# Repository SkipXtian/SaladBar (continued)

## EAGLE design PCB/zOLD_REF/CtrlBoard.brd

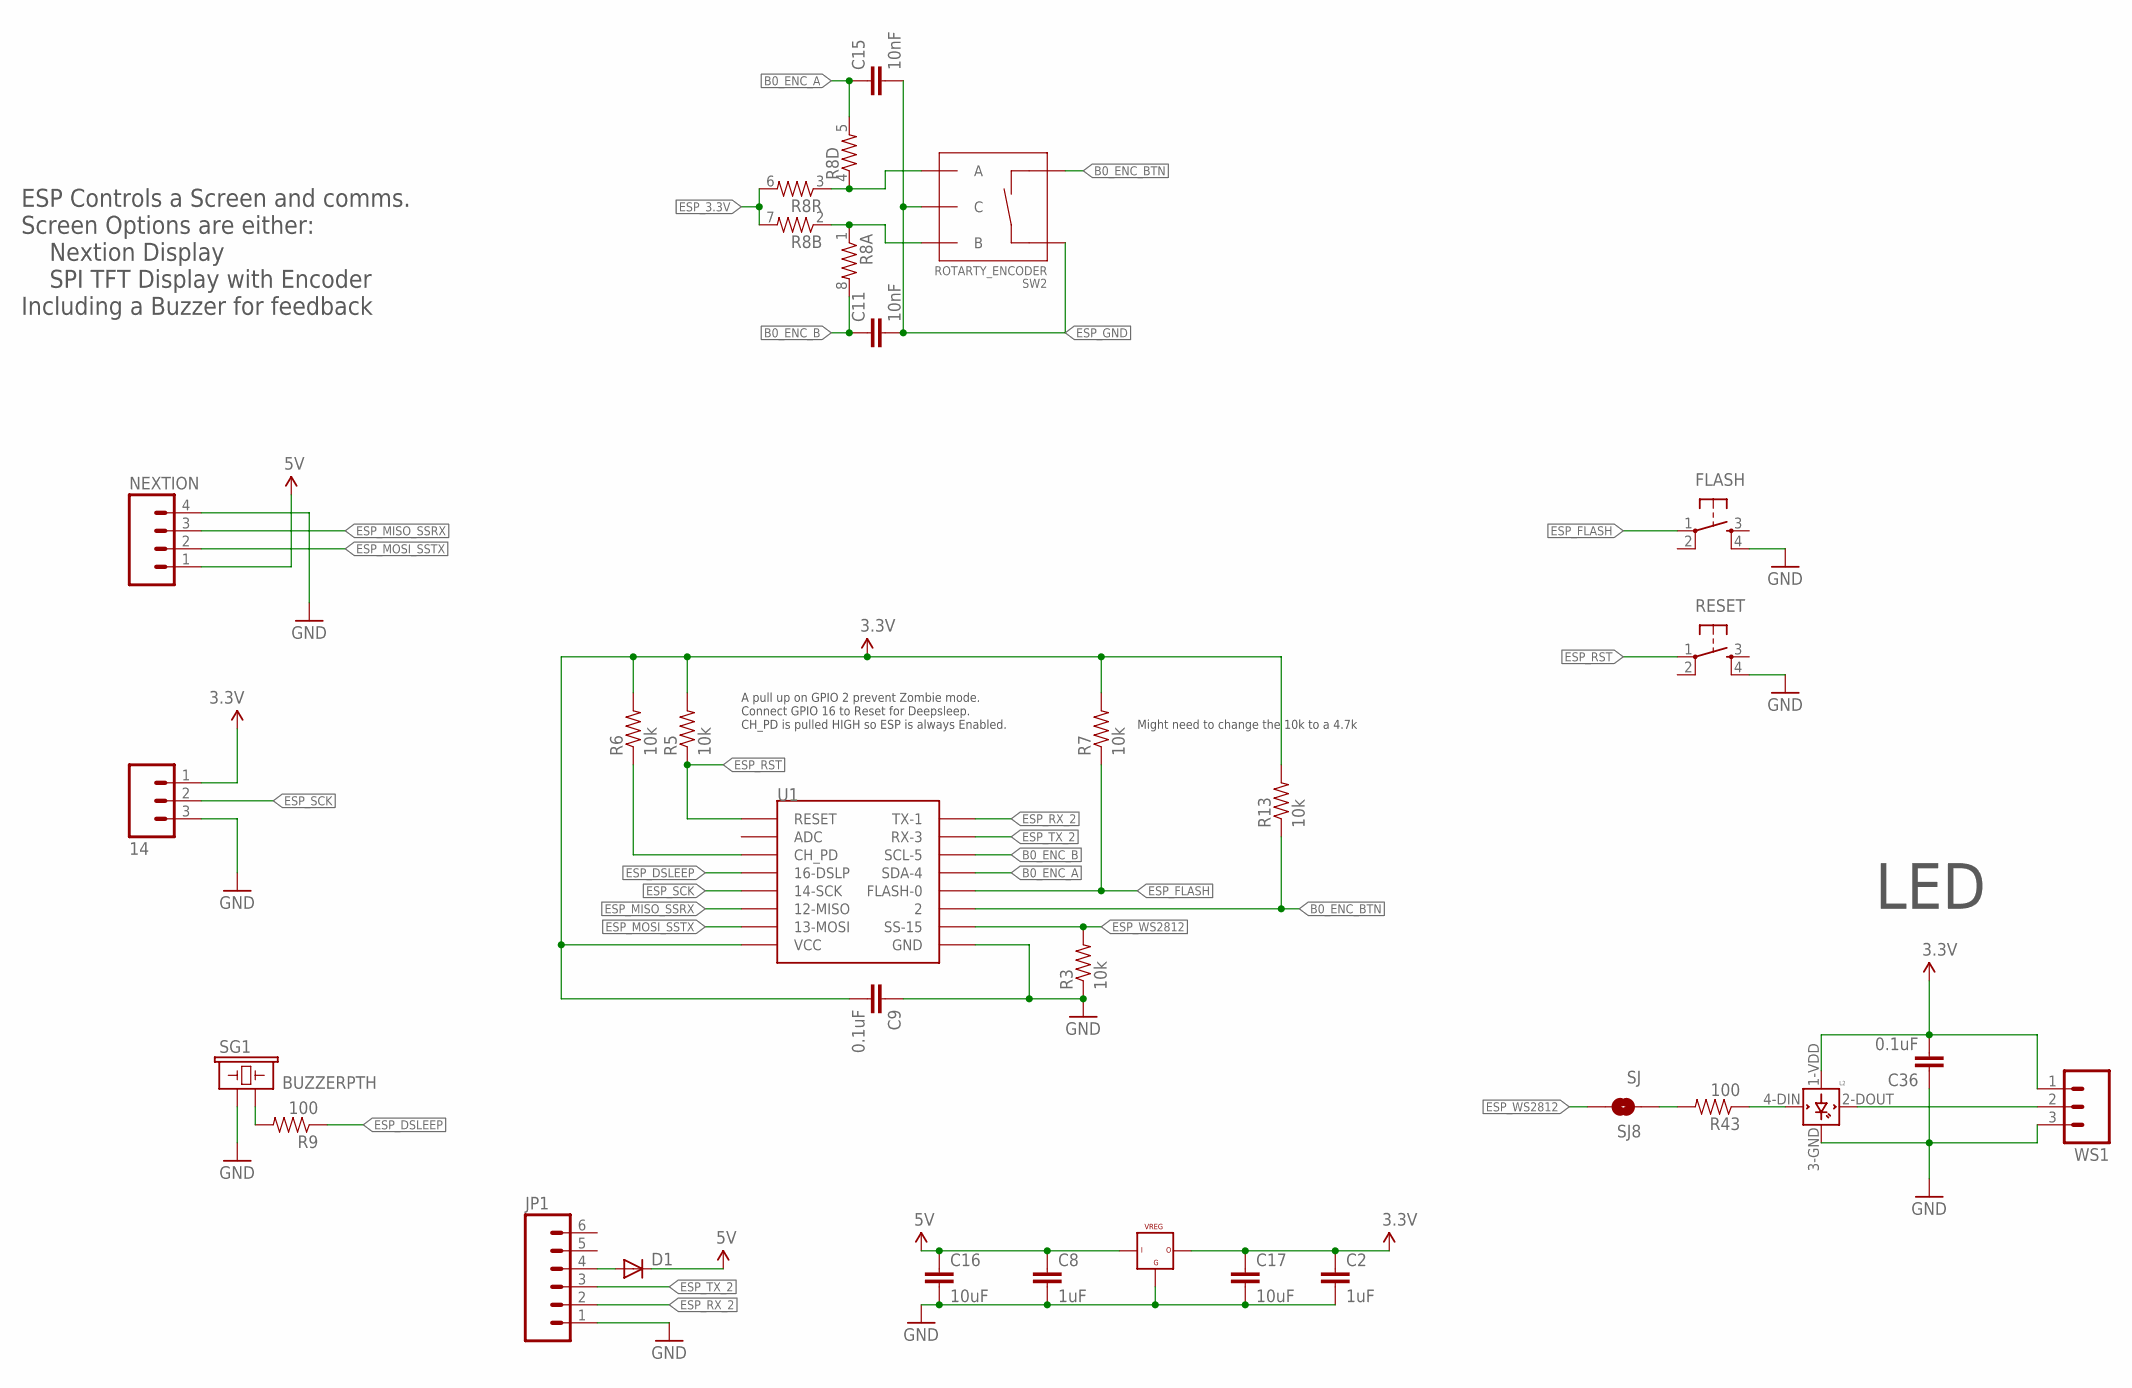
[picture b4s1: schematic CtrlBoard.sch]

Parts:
14: M03PTH; 1X03
C2, C8: 1uF; 0805
C9, C36: 0.1uF; 0805
C11, C15: 10nF; 0805
C16, C17: 10uF; 0805
D1: DIODESOD; SOD-323
FLASH: TAC_SWITCHSMD; TACTILE_SWITCH_SMD
JP1: M06SILK_FEMALE_PTH; 1X06
L2: WS2812B
NEXTION: M041X04_NO_SILK; 1X04_NO_SILK
R3, R5, R6, R7, R13: 10k; 0805
R8: RESISTOR-ARRAY0603-ARV; 0603-ARV
R9, R43: 100; 0805
RESET: TAC_SWITCHSMD; TACTILE_SWITCH_SMD
SG1: BUZZERPTH; BUZZER-12MM
SJ8: SJ; SJ_2S-NO
SW2: ROTARTY_ENCODER; ROTARY_ENC_PLAIN
U1: ESP12SMD; ESP12-SMD
U$3: VREG_3V3; DPACK
WS1: M03PTH; 1X03

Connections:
B0_ENC_A: C15.1, R8.5 (2), U1.GPIO4 (SDA-4)
B0_ENC_B: C11.1, R8.8 (2), U1.GPIO5 (SCL-5)
B0_ENC_BTN: R13.1, SW2.SW-, U1.GPIO2 (2)
ESP_3.3V: 14.1, C2.1, C9.2, C17.1, C36.2, L2.1-VDD (VDD), R5.2, R6.2, R7.2, R8.6 (2), R8.7 (2), R13.2, U1.VCC, U$3.2 (3), WS1.1
ESP_5V: C8.1, C16.1, D1.1 (C), NEXTION.1, U$3.3 (1)
ESP_DSLEEP: R9.1, U1.GPIO16 (16-DSLP)
ESP_FLASH: FLASH.1, R7.1, U1.GPIO0 (FLASH-0)
ESP_GND: 14.3, C2.2, C8.2, C9.1, C11.2, C15.2, C16.2, C17.2, C36.1, FLASH.4, JP1.1, L2.3-GND (GND), NEXTION.4, R3.1, RESET.4, SG1.+ (1), SW2.C, SW2.SW+, U1.GND, U$3.1 (2), WS1.3
ESP_MISO_SSRX: NEXTION.3, U1.GPIO12 (12-MISO)
ESP_MOSI_SSTX: NEXTION.2, U1.GPIO13 (13-MOSI)
ESP_RST: R5.1, RESET.1, U1.RESET
ESP_RX_2: JP1.2, U1.TXD0 (TX-1)
ESP_SCK: 14.2, U1.GPIO14 (14-SCK)
ESP_TX_2: JP1.3, U1.RXD0 (RX-3)
ESP_WS2812: R3.2, SJ8.2, U1.GPIO15 (SS-15)
unnamed: R6.1, U1.CH_PD
unnamed: D1.2 (A), JP1.4
unnamed: R8.1, R8.2 (1), SW2.B
unnamed: R9.2, SG1.- (2)
unnamed: R8.3 (1), R8.4 (1), SW2.A
unnamed: L2.4-DIN (DIN), R43.1
unnamed: L2.2-DOUT (DOUT), WS1.2
unnamed: R43.2, SJ8.1

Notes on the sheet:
A pull up on GPIO 2 prevent Zombie mode. Connect GPIO 16 to Reset for Deepsleep. CH_PD is pulled HIGH so ESP is always Enabled.
Might need to change the 10k to a 4.7k
ESP Controls a Screen and comms. Screen Options are either: Nextion Display SPI TFT Display with Encoder Including a Buzzer for feedback
LED

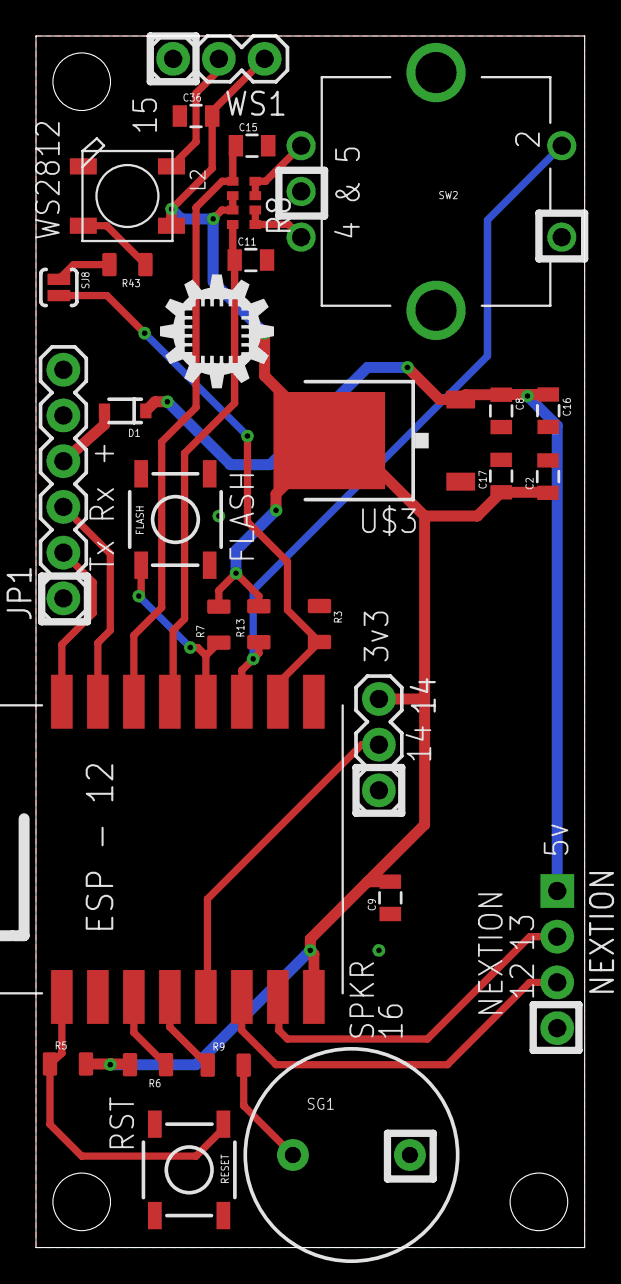
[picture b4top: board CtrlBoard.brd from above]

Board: 2 copper layers, 30.5 x 67.3 mm, 31 parts (1 on the bottom side), 23 nets.

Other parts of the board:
U$19: GCTS_X0.75
U$25: ID_LOGO_X0.25

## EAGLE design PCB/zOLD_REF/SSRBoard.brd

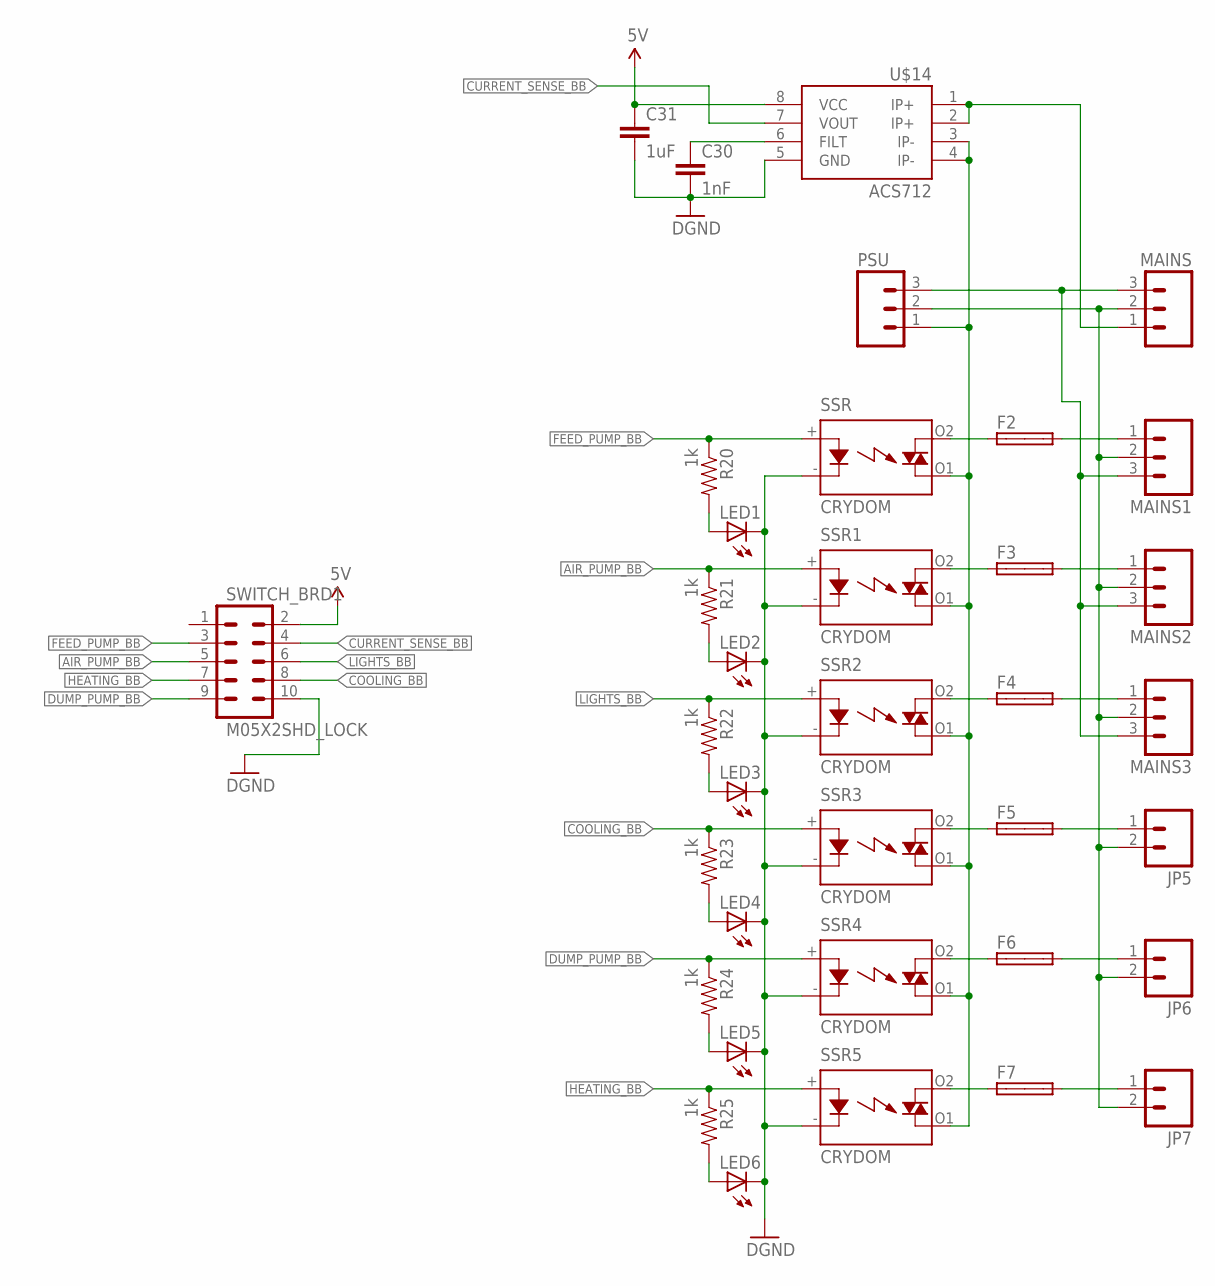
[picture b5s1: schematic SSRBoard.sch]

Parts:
C30: 1nF; 0805
C31: 1uF; 0805
F2, F3, F4, F5, F6, F7: SHK20L
JP5, JP6, JP7: M025MM; SCREWTERMINAL-5MM-2
LED1, LED2, LED3, LED4, LED5, LED6: LEDSML0805; SML0805
MAINS, MAINS1, MAINS2, MAINS3: M03-SCREW-5MM; SCREWTERMINAL-5MM-3
PSU: M03-SCREW-5MM; SCREWTERMINAL-5MM-3
R20, R21, R22, R23, R24, R25: 1k; 0805
SSR: CRYDOM; AQG
SSR1, SSR2, SSR3, SSR4, SSR5: CRYDOM; AQG; MPN AQG22224
SWITCH_BRD1: M05X2SHD_LOCK; 2X5-SHROUDED_LOCK
U$14: ACS712; SO08

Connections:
5V_BB: C31.1, SWITCH_BRD1.2, U$14.8 (VCC)
AIR_PUMP_BB: R21.1, SSR1.+ (A), SWITCH_BRD1.5
COOLING_BB: R23.1, SSR3.+ (A), SWITCH_BRD1.8
CURRENT_SENSE_BB: SWITCH_BRD1.4, U$14.7 (VOUT)
DUMP_PUMP_BB: R24.1, SSR4.+ (A), SWITCH_BRD1.9
FEED_PUMP_BB: R20.1, SSR.+ (A), SWITCH_BRD1.3
GND_BB: C30.2, C31.2, LED1.C, LED2.C, LED3.C, LED4.C, LED5.C, LED6.C, SSR.- (K), SSR1.- (K), SSR2.- (K), SSR3.- (K), SSR4.- (K), SSR5.- (K), SWITCH_BRD1.10, U$14.5 (GND)
HEATING_BB: R25.1, SSR5.+ (A), SWITCH_BRD1.7
LIGHTS_BB: R22.1, SSR2.+ (A), SWITCH_BRD1.6
MAIN_ACTIVE: PSU.1, SSR.O1 (DS2), SSR1.O1 (DS2), SSR2.O1 (DS2), SSR3.O1 (DS2), SSR4.O1 (DS2), SSR5.O1 (DS2), U$14.3 (IP-), U$14.4 (IP-)
MAIN_ACTIVE1: MAINS.1, U$14.1 (IP+), U$14.2 (IP+)
MAIN_EARTH: MAINS.3, MAINS1.3, MAINS2.3, MAINS3.3, PSU.3
MAIN_NETURAL: JP5.2, JP6.2, JP7.2, MAINS.2, MAINS1.2, MAINS2.2, MAINS3.2, PSU.2
unnamed: F3.1A, SSR1.O2 (DS1)
unnamed: F2.1A, SSR.O2 (DS1)
unnamed: F4.1A, SSR2.O2 (DS1)
unnamed: F5.1A, SSR3.O2 (DS1)
unnamed: F6.1A, SSR4.O2 (DS1)
unnamed: F7.1A, SSR5.O2 (DS1)
unnamed: LED1.A, R20.2
unnamed: F2.2A, MAINS1.1
unnamed: F3.2A, MAINS2.1
unnamed: F4.2A, MAINS3.1
unnamed: F5.2A, JP5.1
unnamed: F6.2A, JP6.1
unnamed: F7.2A, JP7.1
unnamed: LED2.A, R21.2
unnamed: LED3.A, R22.2
unnamed: LED4.A, R23.2
unnamed: C30.1, U$14.6 (FILT)
unnamed: LED5.A, R24.2
unnamed: LED6.A, R25.2

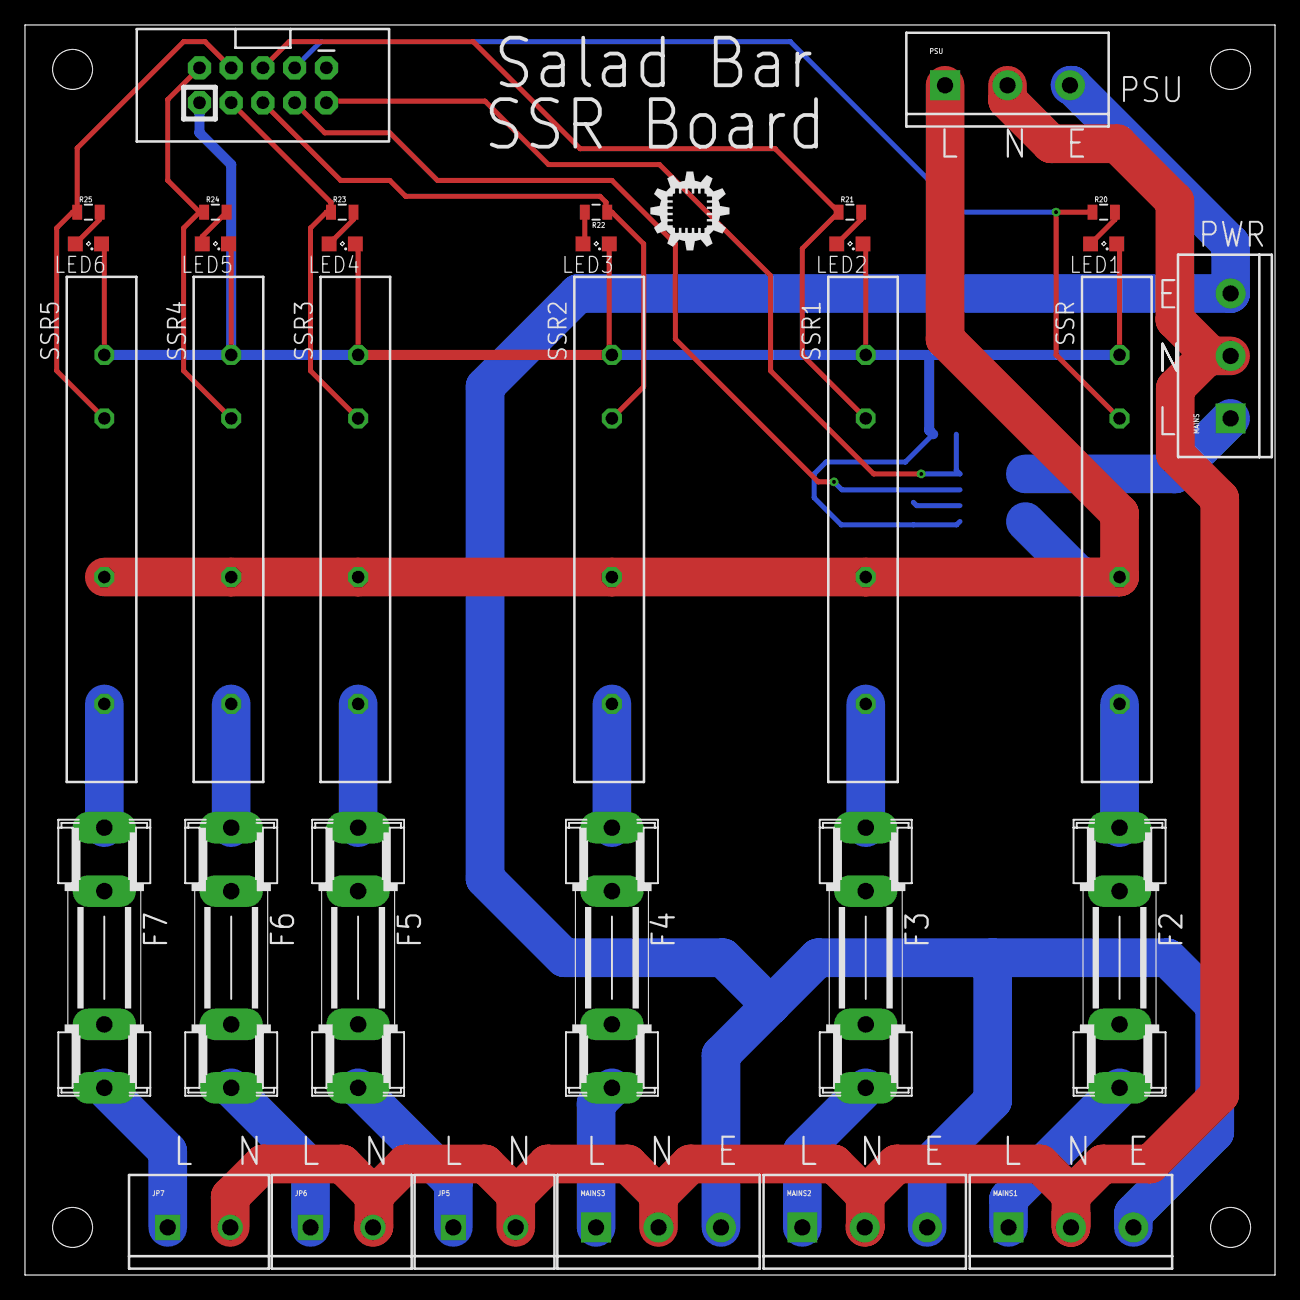
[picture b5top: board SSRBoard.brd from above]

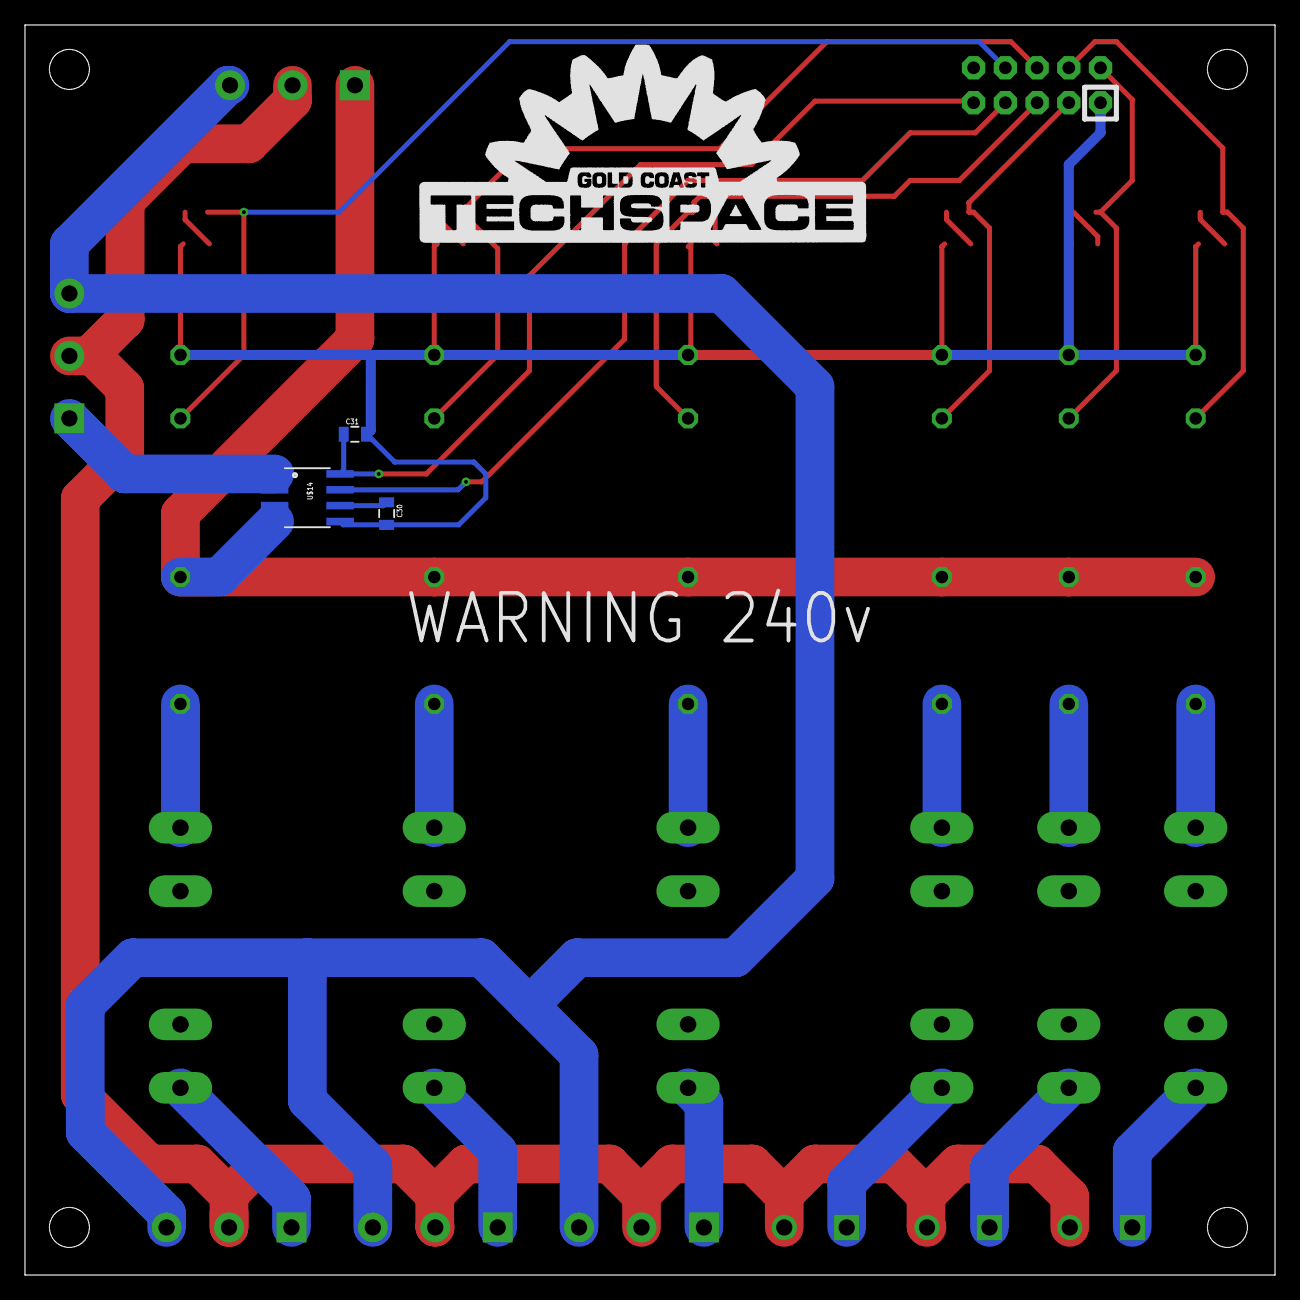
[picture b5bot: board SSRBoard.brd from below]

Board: 2 copper layers, 100.1 x 100.1 mm, 38 parts (4 on the bottom side), 32 nets.

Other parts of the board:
U$21: GCTS_X0.75
U$24: ID_LOGO_X0.25

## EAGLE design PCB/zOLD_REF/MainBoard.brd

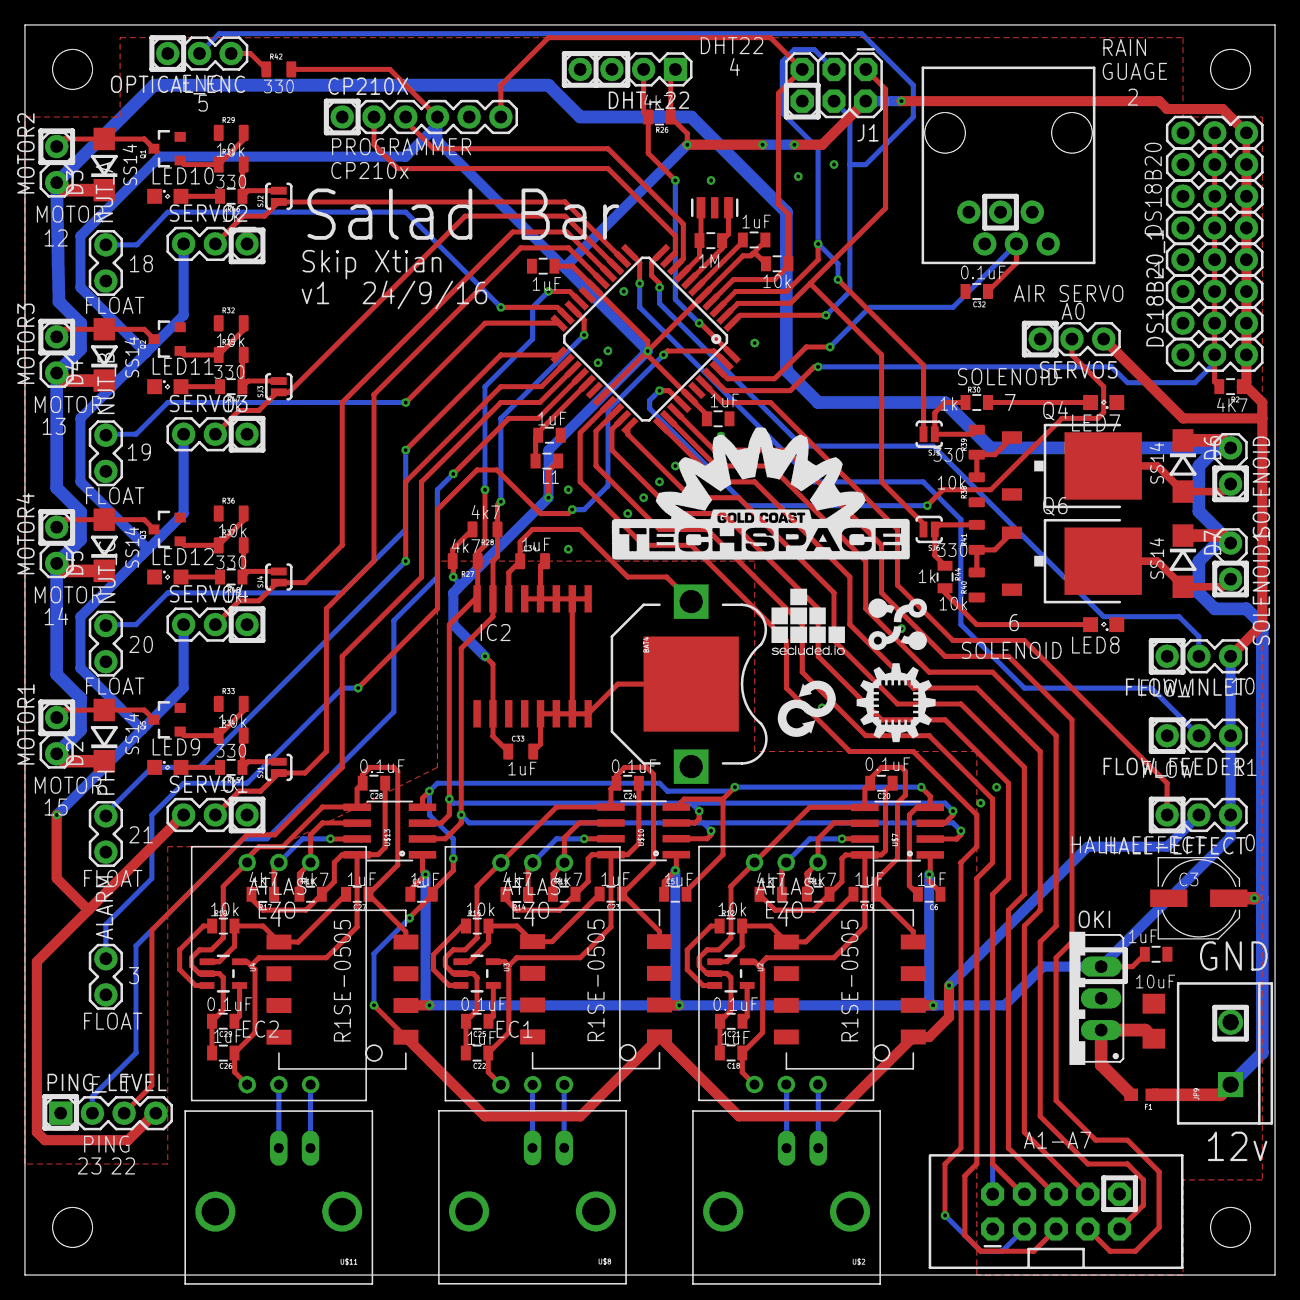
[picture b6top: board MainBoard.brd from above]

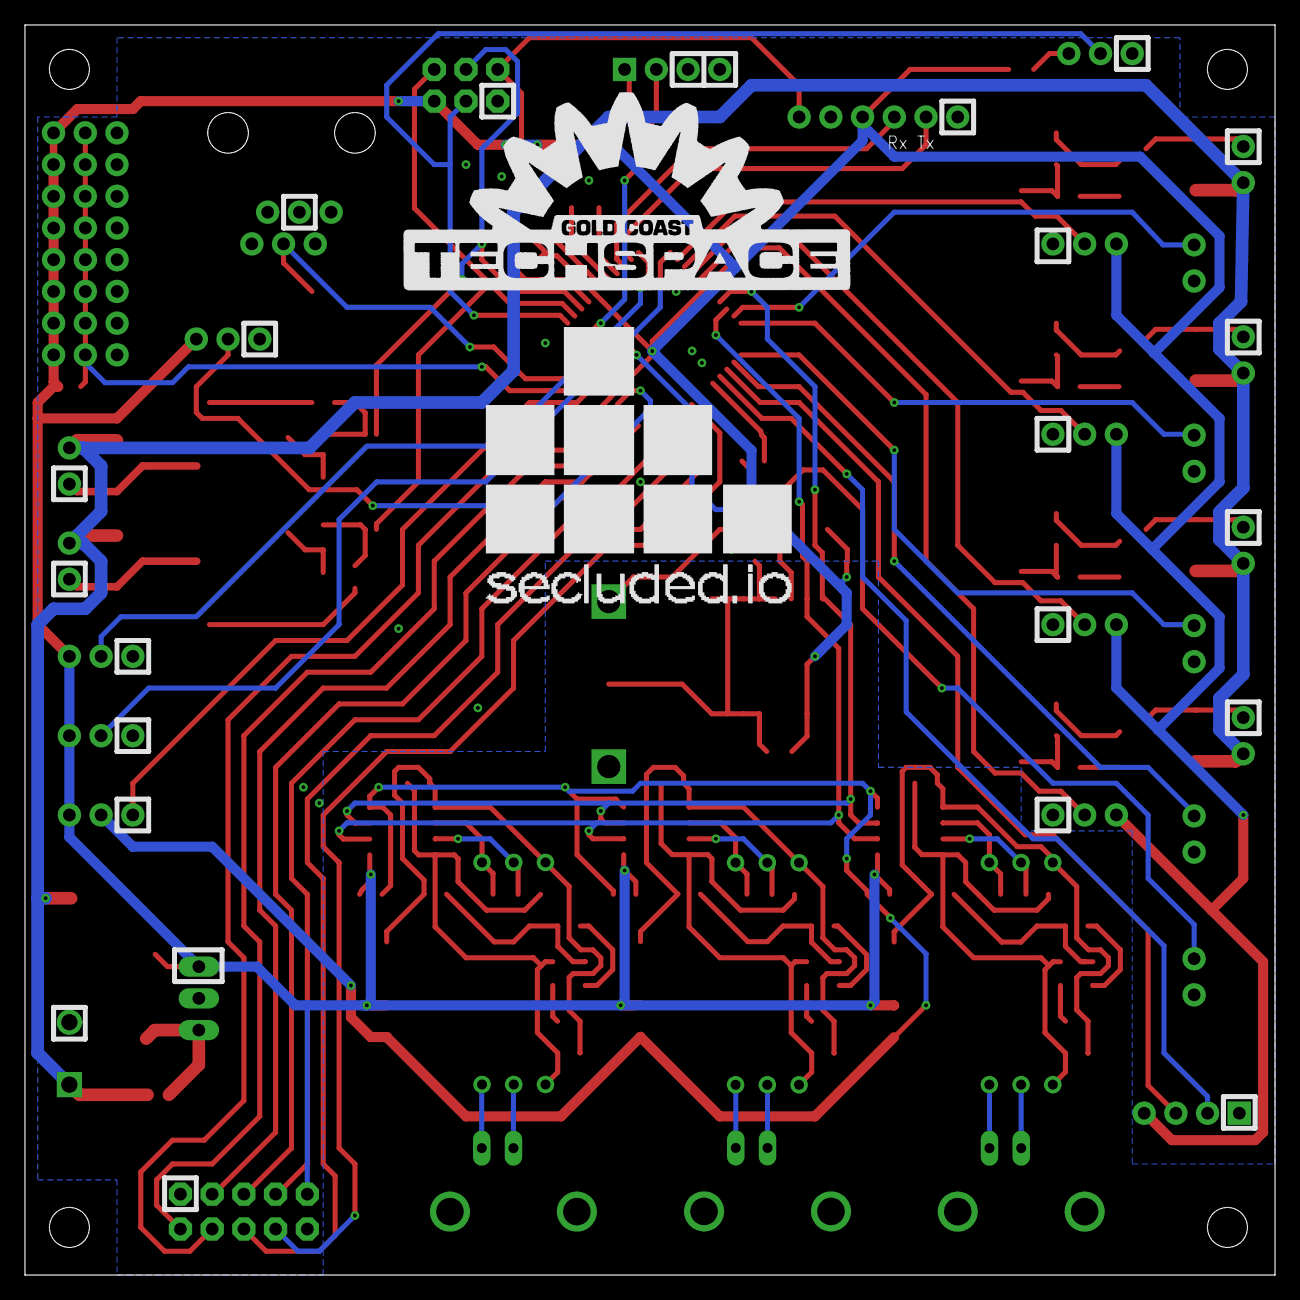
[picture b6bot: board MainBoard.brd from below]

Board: 2 copper layers, 100.1 x 100.1 mm, 147 parts (2 on the bottom side), 93 nets.

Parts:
ALARM: 1X02_LOCK
BAT4: BATTCON_12MM_PTH
C1: 10uF; 1206
C3: PANASONIC_D
C4, C5, C6, C7, C10, C12, C13, C14, C18, C19, C22, C23, C26, C27, C33, C34: 1uF; 0805
C20, C21, C24, C25, C28, C29, C32: 0.1uF; 0805
CP210X: 1X06
D2, D3, D4, D5, D6, D7: SS14; DO214BA
DHT-22: 1X04
DS18B20_1, DS18B20_2, DS18B20_3, DS18B20_4, DS18B20_5, DS18B20_6, DS18B20_7, DS18B20_8: 1X03
EC, EC1: ATLAS-EZO
EC2: ATLAS-EZO
F1: PTC0603; 0603
FLOW_FEEDER: 1X03
FLOW_INLET: 1X03
HALL-EFFECT: 1X03
IC1: ATMEGA644A; TQFP44
IC2: DS3231/SO; SO16W
J1: AVR_SPI_PRG_6PTH; 2X3
JP9: SCREWTERMINAL-5MM-2
L1: 0805
LED7, LED8, LED9, LED10, LED11, LED12: SML0805
MOTOR1, MOTOR2, MOTOR3, MOTOR4: 1X02_LOCK
NUT_A: 1X02_LOCK
NUT_B: 1X02_LOCK
NUT_C: 1X02_LOCK
OKI: 78XXS
OPTICAL_ENC: 1X03
PH: 1X02_LOCK
PING_LEVEL: 1X04
Q1, Q2, Q3, Q5: NTD5867NLT4G; SOT23-3
Q4, Q6: NTD5867NLT4G; DPACK
R1, R12, R16, R19, R29, R32, R33, R36, R38, R40: 10k; 0805
R2: 4K7; 0805
R4: 1M; 0805
R10, R11, R14, R15, R17, R18, R26, R27, R28: 4k7; 0805
R30, R44, R45, R46, R47, R48: 1k; 0805
R31, R34, R35, R37, R39, R41, R42: 330; 0805
RAIN: RJ11-6PTH; RJ11-6
SERVO1, SERVO2, SERVO3, SERVO4, SERVO5: 1X03
SJ1, SJ2, SJ3, SJ4, SJ5, SJ6: SJ; SJ_2S-NO
SOLENOID, SOLENOID1: 1X02_LOCK
SWITCH_BRD2: M05X2SHD_LOCK; 2X5-SHROUDED_LOCK
U2, U3, U4: TPS73150DBVT; SOT23-5
U$1: REFACTORLOOP
U$2, U$8, U$11: BNCPTH; BNC
U$6, U$9, U$12: R1SE-0505
U$7, U$10, U$13: SI860X; SO08
U$15: SECLUDED_5MM
U$17: ESPDUINO_LOGO_5MM
U$18: GCTS_X0.5_TSILK
U$20: ID_LOGO_X0.25
U$22: GCTS_X0.75
U$23: SECLUDED_25MM
Y1: FREQCTRL_RESONATORSMD; FREQCTRL_RESONATOR-SMD

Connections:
5V: C4.1, C5.1, C6.1, C7.1, C12.1, C13.1, C14.1, C33.1, CP210X.4, DHT-22.1, DS18B20_1.1, DS18B20_2.1, DS18B20_3.1, DS18B20_4.1, DS18B20_5.1, DS18B20_6.1, DS18B20_7.1, DS18B20_8.1, FLOW_FEEDER.1, FLOW_INLET.1, HALL-EFFECT.1, IC1.5, IC1.17, IC1.29, IC1.38, IC2.2, J1.2, L1.1, OKI.OUT, PING_LEVEL.4, R1.1, R2.1, R26.1, R27.2, R28.2, R42.2, SERVO1.1, SERVO2.1, SERVO3.1, SERVO4.1, SERVO5.1, SWITCH_BRD2.2, U$6.VCC, U$7.1, U$9.VCC, U$10.1, U$12.VCC, U$13.1
12.0V: C3.+, D2.C, D3.C, D4.C, D5.C, D6.C, D7.C, F1.1, JP9.1, MOTOR1.1, MOTOR2.1, MOTOR3.1, MOTOR4.1, SOLENOID.1, SOLENOID1.1
AIR: IC1.37, SERVO5.2
AIR_PUMP: IC1.31, SWITCH_BRD2.5
COOLING: IC1.34, SWITCH_BRD2.8
CURRENT_SENSE: IC1.32, SWITCH_BRD2.4
D1: D3.A, MOTOR2.2, Q1.3
D2: D4.A, MOTOR3.2, Q2.3
D3: D5.A, MOTOR4.2, Q3.3
D4: D2.A, MOTOR1.2, Q5.3
D5: D6.A, Q4.2, SOLENOID.2
D6: D7.A, Q6.2, SOLENOID1.2
DHT22: DHT-22.2, IC1.44, R26.2
DUMP_HALL-EFFECT: HALL-EFFECT.3, IC1.40
DUMP_PUMP: IC1.35, SWITCH_BRD2.9
FEEDER_FLOW: FLOW_FEEDER.2, IC1.12
FEED_PUMP: IC1.30, SWITCH_BRD2.3
FLOAT_LEVEL-ALARM: ALARM.1, IC1.43
FLOAT_NUT_A: IC1.21, NUT_A.1
FLOAT_NUT_B: IC1.22, NUT_B.1
FLOAT_NUT_C: IC1.23, NUT_C.1
FLOAT_PH_DOWN: IC1.24, PH.1
GND: ALARM.2, BAT4.GND, C1.2, C3.-, C4.2, C5.2, C6.2, C7.2, C10.2, C12.2, C13.2, C14.2, C32.2, C33.2, C34.2, CP210X.1, DHT-22.3, DHT-22.4, DS18B20_1.3, DS18B20_2.3, DS18B20_3.3, DS18B20_4.3, DS18B20_5.3, DS18B20_6.3, DS18B20_7.3, DS18B20_8.3, FLOW_FEEDER.3, FLOW_INLET.3, HALL-EFFECT.2, IC1.6, IC1.18, IC1.28, IC1.39, IC2.5, IC2.6, IC2.7, IC2.8, IC2.9, IC2.10, IC2.11, IC2.12, IC2.13, J1.6, JP9.2, LED7.C, LED8.C, LED9.C, LED10.C, LED11.C, LED12.C, NUT_A.2, NUT_B.2, NUT_C.2, OKI.GND, OPTICAL_ENC.3, PH.2, PING_LEVEL.1, Q1.2, Q2.2, Q3.2, Q4.3, Q5.2, Q6.3, R29.1, R32.1, R33.1, R36.1, R38.1, R40.1, RAIN.4, SERVO1.3, SERVO2.3, SERVO3.3, SERVO4.3, SERVO5.3, SWITCH_BRD2.1, SWITCH_BRD2.10, U$6.GND, U$7.4, U$9.GND, U$10.4, U$12.GND, U$13.4, Y1.2
HEATING: IC1.36, SWITCH_BRD2.7
INLET_FLOW: FLOW_INLET.2, IC1.11
LEVEL_PING-ECHO: IC1.26, PING_LEVEL.2
LEVEL_PING-TRIG: IC1.25, PING_LEVEL.3
LIGHTS: IC1.33, SWITCH_BRD2.6
unnamed: IC1.7, R4.2, Y1.1
unnamed: IC1.8, R4.1, Y1.3
unnamed: EC.PRA, U$2.GND
unnamed: EC.PRB, U$2.S
unnamed: C18.2, C19.1, C20.2, C21.2, EC.GND, U2.2, U$6.ISO_GND, U$7.5
unnamed: C18.1, C20.1, EC.VCC, R10.2, R11.2, U2.5, U$7.8
unnamed: EC.RX, R11.1, U$7.6
unnamed: C10.1, IC1.27, L1.2
unnamed: EC.TX, R10.1, U$7.7
unnamed: R12.1, U2.3
unnamed: C19.2, R12.2, U2.1, U$6.ISO_VCC
unnamed: C1.1, F1.2, OKI.IN
unnamed: EC1.PRB, U$8.S
unnamed: C21.1, U2.4
unnamed: C22.2, C23.1, C24.2, C25.2, EC1.GND, U3.2, U$9.ISO_GND, U$10.5
unnamed: C22.1, C24.1, EC1.VCC, R14.2, R15.2, U3.5, U$10.8
unnamed: EC1.PRA, U$8.GND
unnamed: EC1.RX, R15.1, U$10.6
unnamed: EC1.TX, R14.1, U$10.7
unnamed: C23.2, R16.2, U3.1, U$9.ISO_VCC
unnamed: C25.1, U3.4
unnamed: R16.1, U3.3
unnamed: EC2.PRB, U$11.S
unnamed: C26.2, C27.1, C28.2, C29.2, EC2.GND, U4.2, U$12.ISO_GND, U$13.5
unnamed: C26.1, C28.1, EC2.VCC, R17.2, R18.2, U4.5, U$13.8
unnamed: EC2.PRA, U$11.GND
unnamed: EC2.RX, R18.1, U$13.6
unnamed: EC2.TX, R17.1, U$13.7
unnamed: C27.2, R19.2, U4.1, U$12.ISO_VCC
unnamed: C29.1, U4.4
unnamed: R19.1, U4.3
unnamed: BAT4.VCC@1, C34.1, IC2.14
unnamed: Q5.1, R33.2, R34.1
unnamed: LED7.A, R30.2
unnamed: Q1.1, R29.2, R31.1
unnamed: R34.2, R45.1, SJ1.2
unnamed: R31.2, R46.1, SJ2.2
unnamed: Q2.1, R32.2, R35.1
unnamed: R35.2, R47.1, SJ3.2
unnamed: Q3.1, R36.2, R37.1
unnamed: R37.2, R48.1, SJ4.2
unnamed: Q4.1, R38.2, R39.1
unnamed: Q6.1, R40.2, R41.1
unnamed: LED8.A, R44.2
unnamed: LED9.A, R45.2
unnamed: R30.1, R39.2, SJ5.1
unnamed: R41.2, R44.1, SJ6.1
unnamed: LED11.A, R47.2
unnamed: OPTICAL_ENC.1, R42.1
unnamed: LED10.A, R46.2
unnamed: LED12.A, R48.2
NUT_A: IC1.13, SERVO2.2, SJ2.1
NUT_B: IC1.14, SERVO3.2, SJ3.1
NUT_C: IC1.15, SERVO4.2, SJ4.1
OPTICAL_ENC: IC1.1, J1.4, OPTICAL_ENC.2
PH_DOWN: IC1.16, SERVO1.2, SJ1.1
PROBE_SCL: IC1.19, IC2.16, R27.1, U$7.3, U$10.3, U$13.3
PROBE_SDA: IC1.20, IC2.15, R28.1, U$7.2, U$10.2, U$13.2
RAIN_GUAGE: C32.1, IC1.42, RAIN.3
RST: CP210X.6, IC1.4, J1.5, R1.2
RX: CP210X.3, IC1.9
SOLENOID: IC1.3, J1.3, SJ5.2
SOLENOID1: IC1.2, J1.1, SJ6.2
TEMP: DS18B20_1.2, DS18B20_2.2, DS18B20_3.2, DS18B20_4.2, DS18B20_5.2, DS18B20_6.2, DS18B20_7.2, DS18B20_8.2, IC1.41, R2.2
TX: CP210X.2, IC1.10

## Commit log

2017-06-21 Initial
2017-07-14 added panel and start of Lighting controller
